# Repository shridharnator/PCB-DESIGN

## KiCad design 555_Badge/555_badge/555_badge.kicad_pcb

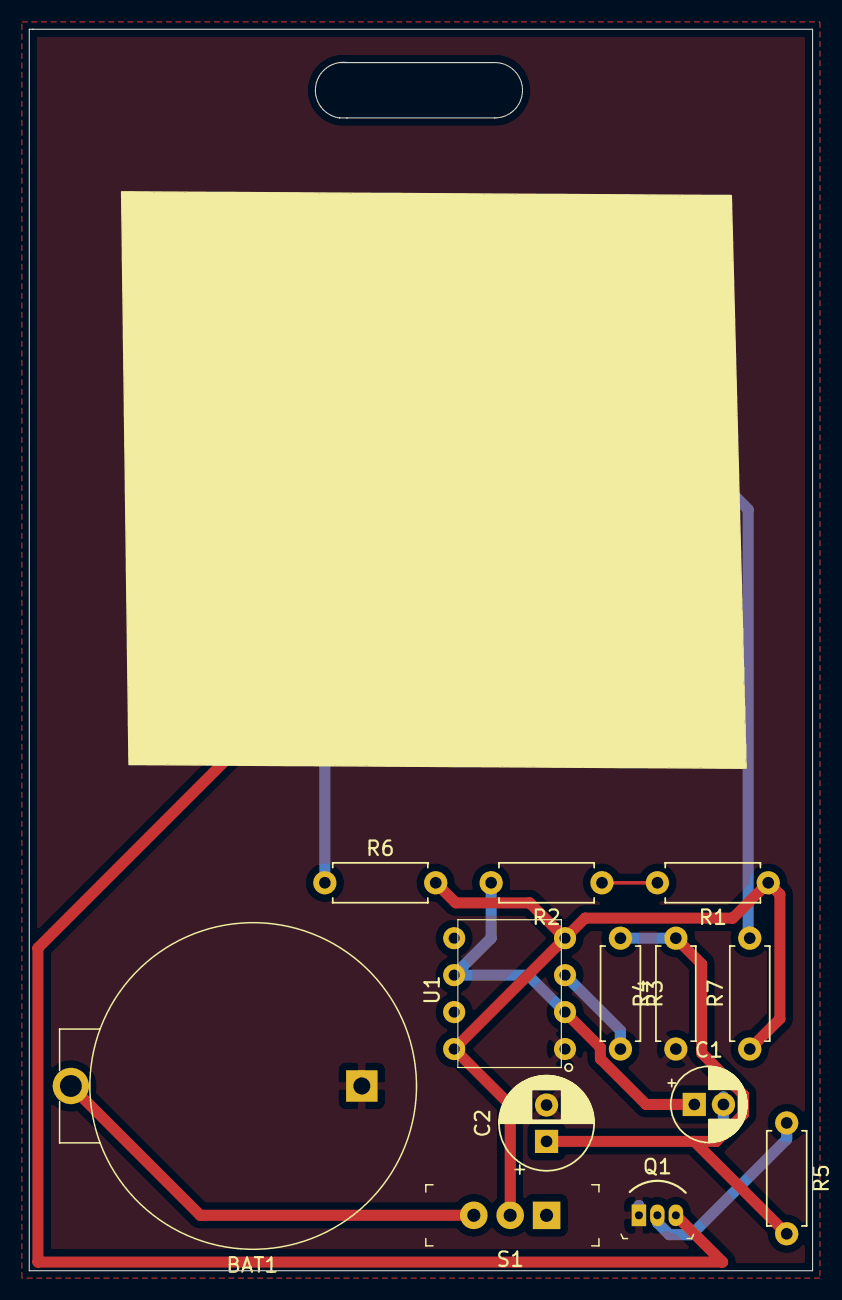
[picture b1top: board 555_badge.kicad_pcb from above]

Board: 2 copper layers, 53.8 x 85.3 mm, 15 parts (0 on the bottom side), 11 nets.

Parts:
BAT1: BS-7; Battery_Holder_Coin_2032_BS-7
C1: 10uF; CP_Radial_D5.0mm_P2.00mm
C2: 100uF; CP_Radial_D6.3mm_P2.50mm
D1, D2: RED; LED_3mm_Radial
Q1: 2N3904; TO-92-3
R1, R3: 22k; R_Axial_DIN0207_L6.3mm_D2.5mm_P7.62mm_Horizontal
R2: 330k; R_Axial_DIN0207_L6.3mm_D2.5mm_P7.62mm_Horizontal
R4: 100k; R_Axial_DIN0207_L6.3mm_D2.5mm_P7.62mm_Horizontal
R5: 10k; R_Axial_DIN0207_L6.3mm_D2.5mm_P7.62mm_Horizontal
R6, R7: 100; R_Axial_DIN0207_L6.3mm_D2.5mm_P7.62mm_Horizontal
S1: EG1218; Switch_Slide_11.6x4mm_EG1218
U1: 7555; ICM7555-PDIP

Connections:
GND: BAT1.Neg, C1.2, C2.2, Q1.1, R4.1, U1.1
unnamed: BAT1.Pos, S1.3
unnamed: C1.1, R2.2, U1.2, U1.6
unnamed: C2.1, R3.1, R4.2, R5.2
unnamed: D1.1, D2.1, Q1.3
unnamed: D1.2, R6.1
unnamed: D2.2, R7.2
unnamed: Q1.2, R5.1
unnamed: R1.2, R2.1
unnamed: R3.2, U1.3
VCC: R1.1, R6.2, R7.1, S1.2, U1.4, U1.8

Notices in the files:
555_Badge/555_badge/555_badge.kicad_pcb:
Liscence CC BY 4.0
